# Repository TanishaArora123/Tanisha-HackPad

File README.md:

Tanisha A's macropad.
This macropad has 6 keys with an OLED display. I will use it for keyboard shortcuts. 

Features: I am planning on printing the different parts with different colors of filament.

The case has both a bottom and top panel and they can be screwed together. 

Schematic:

PCB: 

Case (made on onshape):

BOM:
1x seeed xiao rp2040

1x 1x04 pinheader

9x tht diodes

9x 1.00u cherry mx switches
4x 3.2mm screws

4X 3.2mm Bolts

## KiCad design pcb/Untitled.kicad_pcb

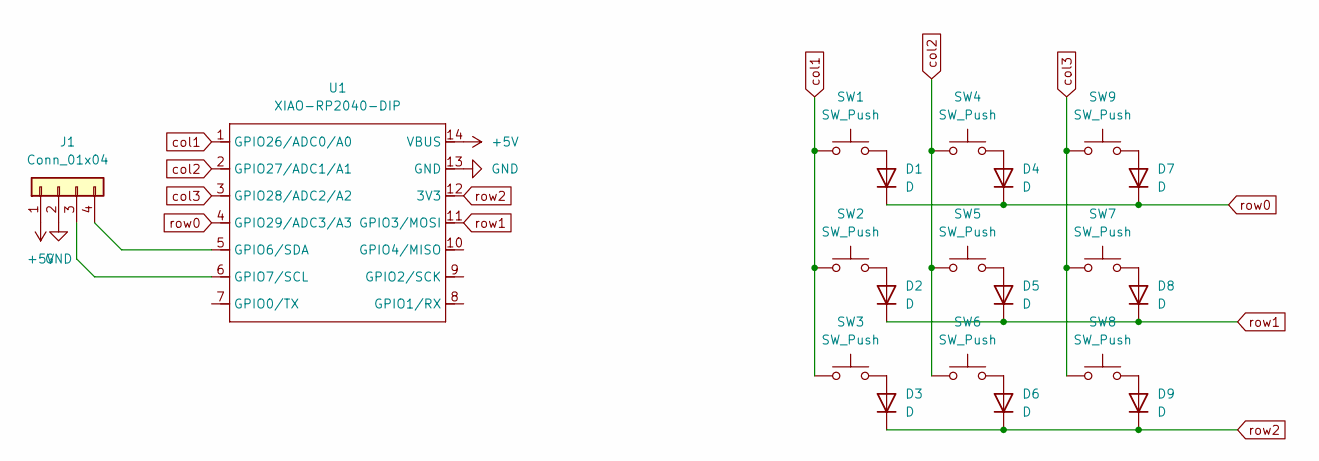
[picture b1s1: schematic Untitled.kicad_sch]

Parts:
D1, D2, D3, D4, D5, D6, D7, D8, D9: D; D_DO-35_SOD27_P7.62mm_Horizontal
J1: Conn_01x04; PinSocket_1x04_P2.54mm_Vertical
SW1, SW2, SW3, SW4, SW5, SW6, SW7, SW8, SW9: SW_Push; SW_Cherry_MX_1.00u_PCB
U1: XIAO-RP2040-DIP

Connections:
+5V: J1.1, U1.14 (VBUS)
GND: J1.2, U1.13 (GND)
unnamed: D1.2 (A), SW1.2
unnamed: D2.2 (A), SW2.2
unnamed: D3.2 (A), SW3.2
unnamed: D4.2 (A), SW4.2
unnamed: D5.2 (A), SW5.2
unnamed: D6.2 (A), SW6.2
unnamed: D7.2 (A), SW9.2
unnamed: D8.2 (A), SW7.2
unnamed: D9.2 (A), SW8.2
unnamed: J1.3, U1.6 (GPIO7/SCL)
unnamed: J1.4, U1.5 (GPIO6/SDA)
col1: SW1.1, SW2.1, SW3.1, U1.1 (GPIO26/ADC0/A0)
col2: SW4.1, SW5.1, SW6.1, U1.2 (GPIO27/ADC1/A1)
col3: SW7.1, SW8.1, SW9.1, U1.3 (GPIO28/ADC2/A2)
row0: D1.1 (K), D4.1 (K), D7.1 (K), U1.4 (GPIO29/ADC3/A3)
row1: D2.1 (K), D5.1 (K), D8.1 (K), U1.11 (GPIO3/MOSI)
row2: D3.1 (K), D6.1 (K), D9.1 (K), U1.12 (3V3)

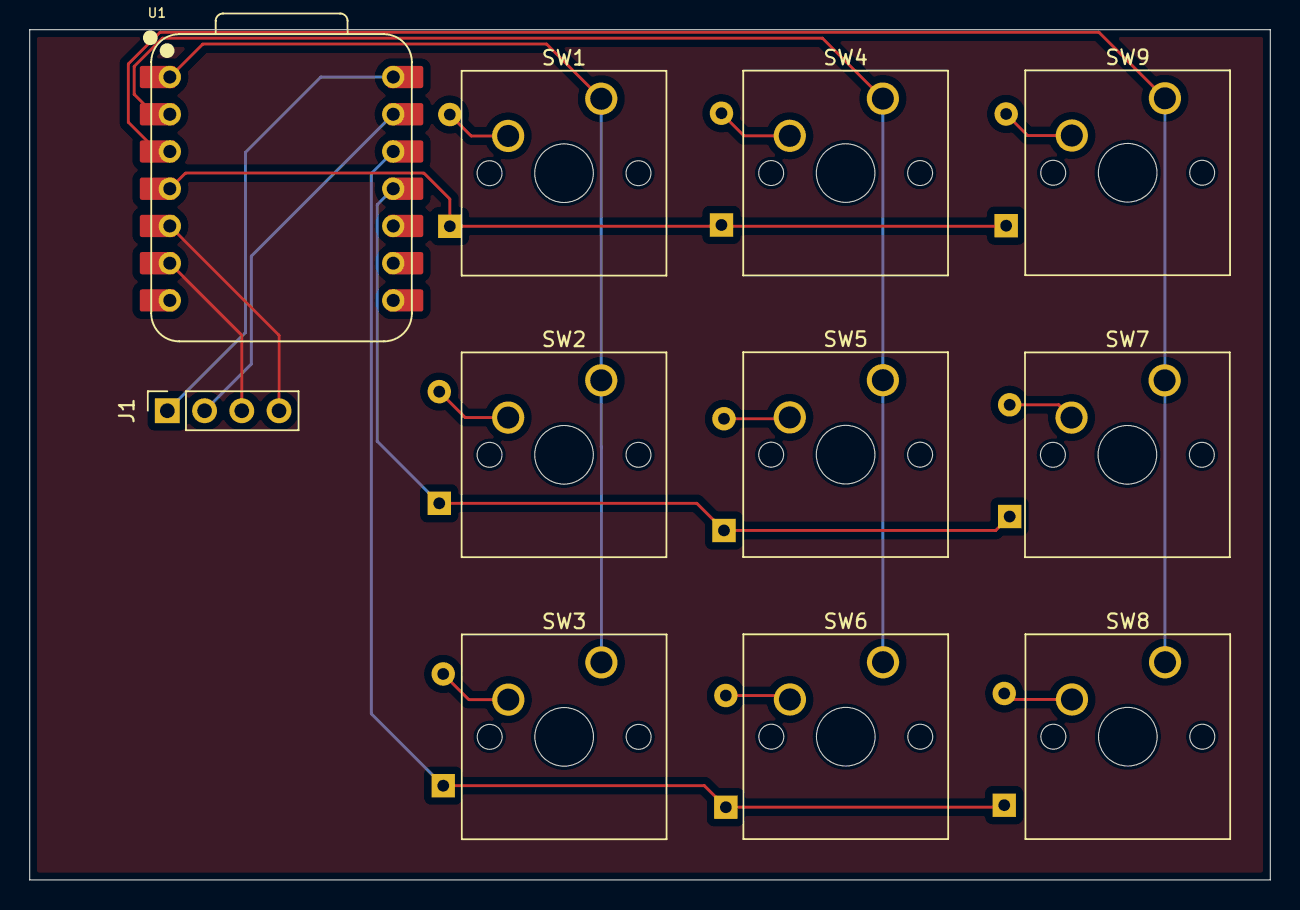
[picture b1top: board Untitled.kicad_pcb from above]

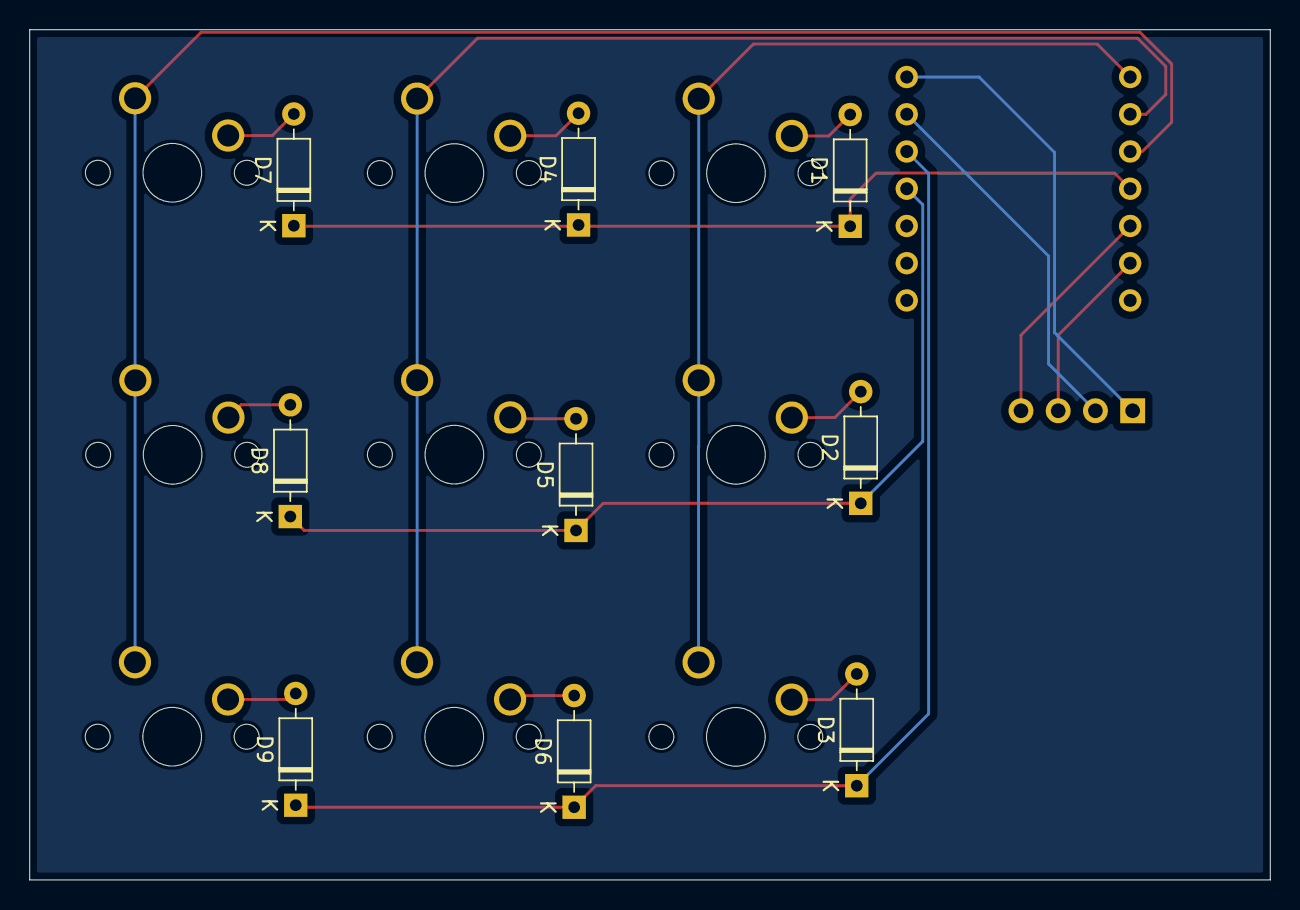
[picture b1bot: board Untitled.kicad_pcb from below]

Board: 2 copper layers, 84.6 x 58.0 mm, 20 parts (9 on the bottom side), 19 nets.

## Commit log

2025-07-10 Create CAD
2025-07-10 Create file
2025-07-10 Create FirmwareKMK
